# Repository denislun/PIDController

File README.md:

# Thermocouple PID Controller

A PID controller based on an Arduino using a MAX6675 Thermocouple module.

Current temperature and setpoint will be shown on the LCD display, along with current output state.

## Parts List

* Atmel Atmega328p MCU
* PCD8544 LCD Screen
* MAX6675 Thermocouple interface chip
* Rotary Encoder
* Relay to drive the output

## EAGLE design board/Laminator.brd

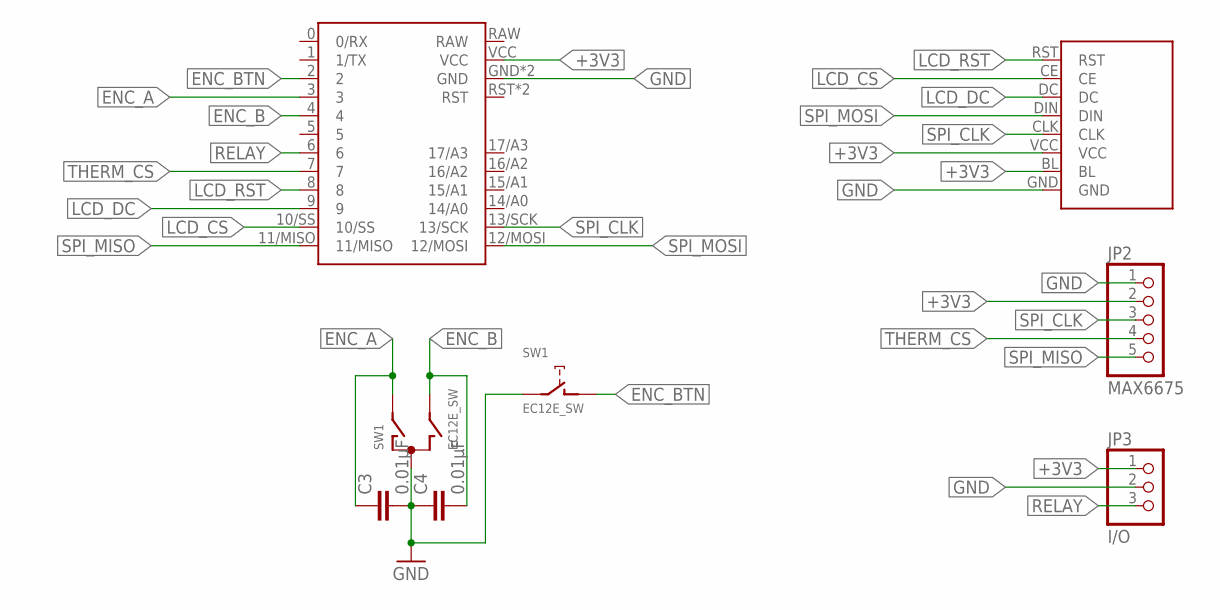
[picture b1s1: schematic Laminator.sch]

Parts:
ARDUINO: ARDUINO_PRO_MINI_DIL; ARDUINO_PRO_MINI_B
C3, C4: 0.01µF; C025-025X050
JP2: MAX6675; 1X05
JP3: I/O; 1X03
SW1: EC12E_SW; ALPS_EC12E_SW
U$1: NOKIA_5110

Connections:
+3V3: ARDUINO.VCC, JP2.2, JP3.1, U$1.BL, U$1.VCC
ENC_A: ARDUINO.3, C3.1, SW1.A
ENC_B: ARDUINO.4, C4.2, SW1.B
ENC_BTN: ARDUINO.2, SW1.D (1)
GND: ARDUINO.GND, ARDUINO.GND@2 (GND), C3.2, C4.1, JP2.1, JP3.2, SW1.C, SW1.E (2), U$1.GND
LCD_CS: ARDUINO.10/SS, U$1.CE
LCD_DC: ARDUINO.9, U$1.DC
LCD_RST: ARDUINO.8, U$1.RST
RELAY: ARDUINO.6, JP3.3
SPI_CLK: ARDUINO.13/SCK, JP2.3, U$1.CLK
SPI_MISO: ARDUINO.11/MISO, JP2.5
SPI_MOSI: ARDUINO.12/MOSI, U$1.DIN
THERM_CS: ARDUINO.7, JP2.4

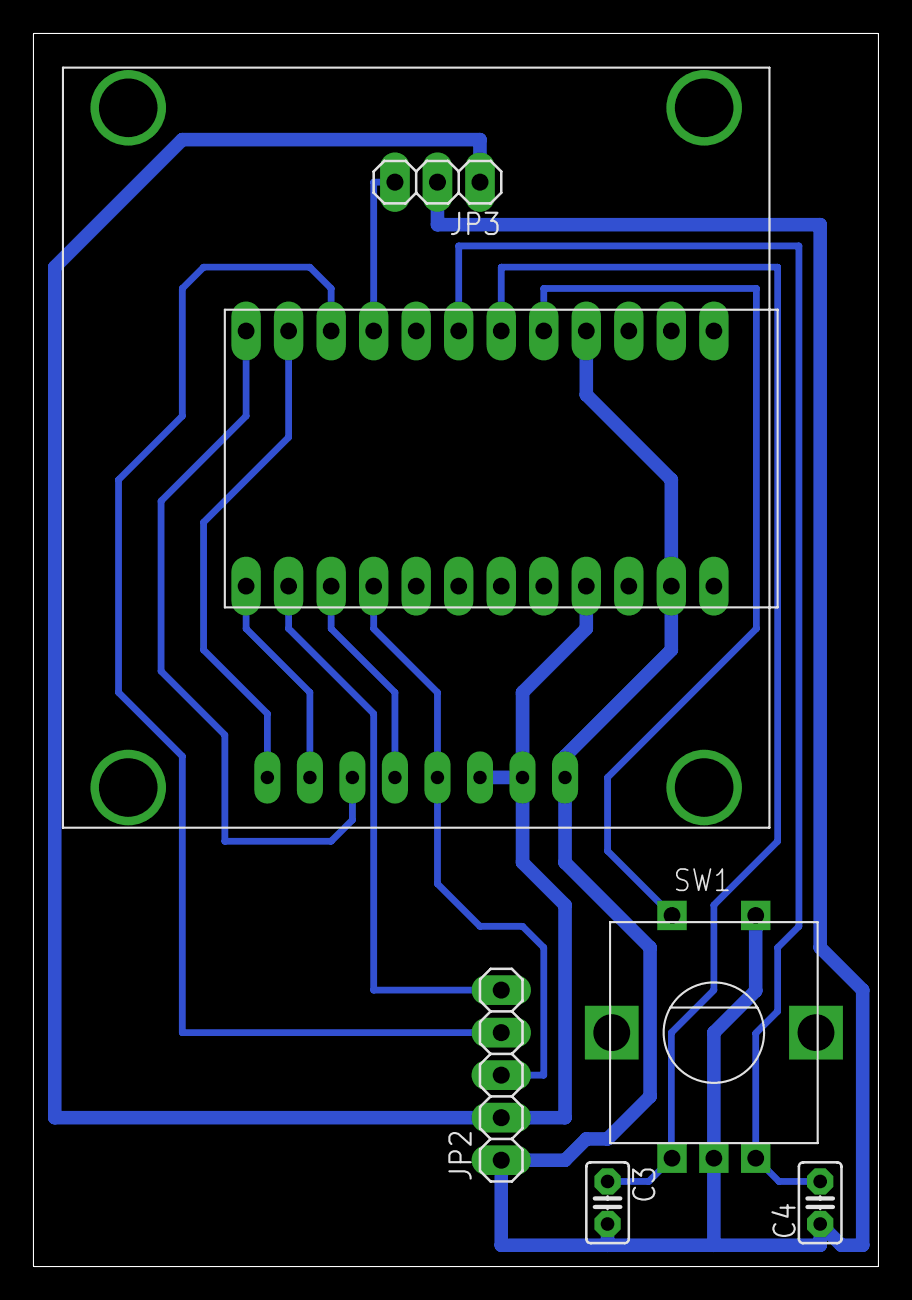
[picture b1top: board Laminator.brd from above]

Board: 2 copper layers, 50.5 x 73.7 mm, 7 parts (0 on the bottom side), 13 nets.

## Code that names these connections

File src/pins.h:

#ifndef _PINS_H
#define _PINS_H

#define SPI_CLK 13
#define SPI_MISO 12
#define SPI_MOSI 11

#define THERMOCOUPLE_CS 8

#define LCD_DC 14
#define LCD_CS 15
#define LCD_RST 16

#define ENCODER_A 4
#define ENCODER_B 3
#define ENCODER_BTN 2

#define RELAY 6

#endif

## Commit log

2016-06-07 Update for prototype board
2016-06-07 Add board and schematic
2016-06-07 Add readme and schematic png
2016-07-25 Better use of hardware SPI
    * Remove bitbanging MAX6675 library
    * Modify Adafruit_PCD8544 to use SPI transactions
    * Add Thermocouple library & use SPI transactions
2016-07-25 Update parts list to match updated project
